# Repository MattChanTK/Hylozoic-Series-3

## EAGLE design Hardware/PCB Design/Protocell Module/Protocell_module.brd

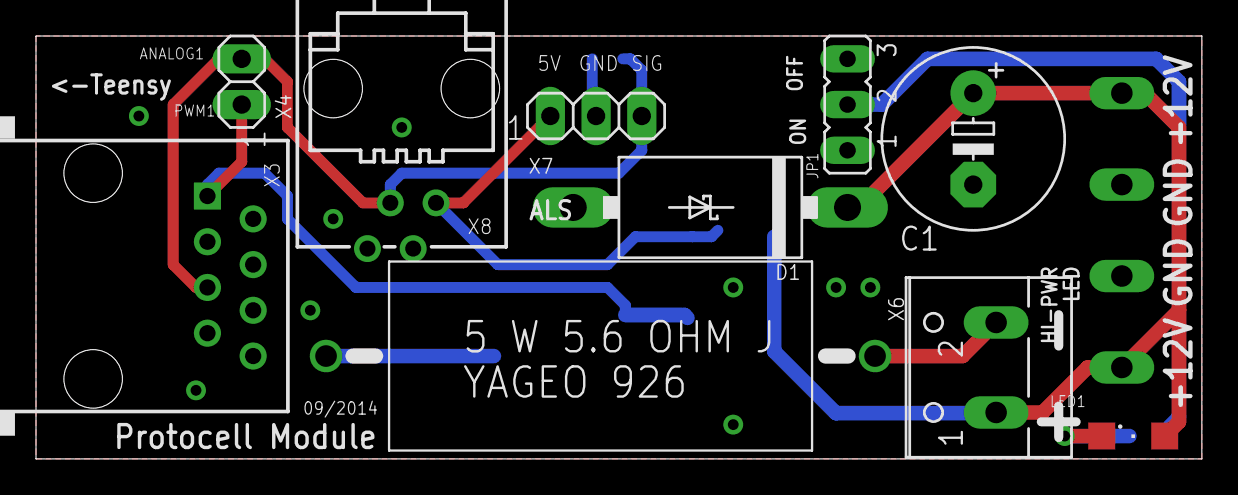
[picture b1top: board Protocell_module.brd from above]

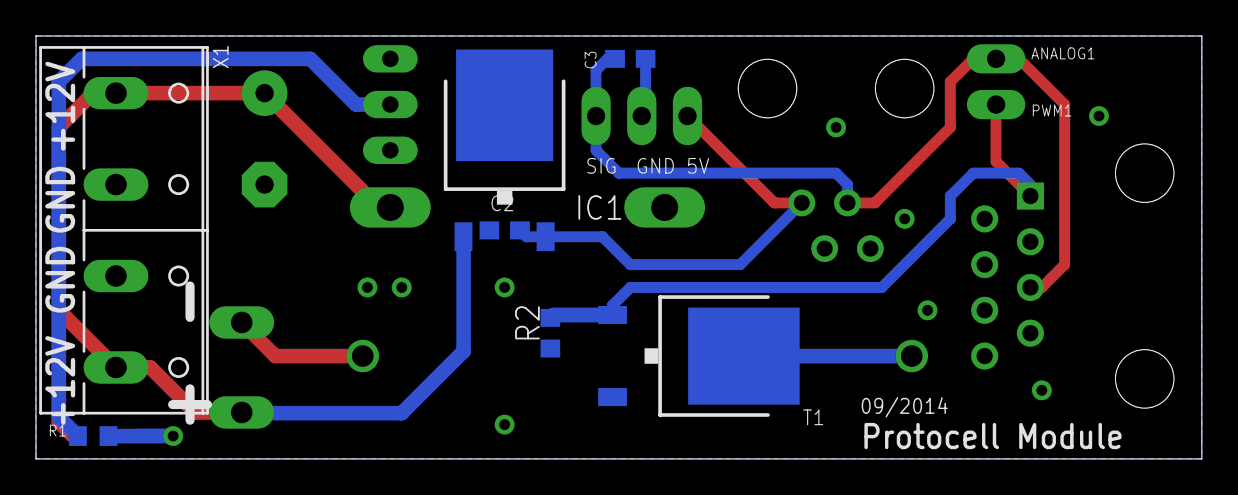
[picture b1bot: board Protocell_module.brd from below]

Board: 2 copper layers, 64.8 x 23.5 mm, 17 parts (7 on the bottom side), 9 nets.

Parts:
C1: 470uF; E5-10,5
C2, C3: 1uF; C0603
D1: SB540E-G; DO201T15
IC1: MC7805BDTRKG; DPACK_3
JP1: JP2
LED1: SML1206
R1: 470; R0603
R2: 4.7k; R0603
R3: 5.6; YAGEO_SQP500JB
T1: DPACK
X1: W237-4P
X3: RJ45-8X; RJ45-NO-SHIELD
X4: 1X02
X6: W237-102
X7: 1X03
X8: 558872-1

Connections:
+5V: C2.1, IC1.3, X7.1, X8.1
+12V: C1.+, D1.C, IC1.1, LED1.A, X1.1, X1.4, X6.1
ANALOG1: C3.1, X3.5, X4.2, X7.3, X8.3
GND: C1.-, C2.2, C3.2, D1.A, IC1.4, JP1.1, R2.1, T1.3, X1.2, X1.3, X7.2, X8.2
unnamed: R3.1, T1.2
unnamed: R3.2, X6.2
unnamed: LED1.C, R1.2
PWM1: R2.2, T1.1, X3.1, X4.1
PWR_LED_GND: JP1.2, R1.1

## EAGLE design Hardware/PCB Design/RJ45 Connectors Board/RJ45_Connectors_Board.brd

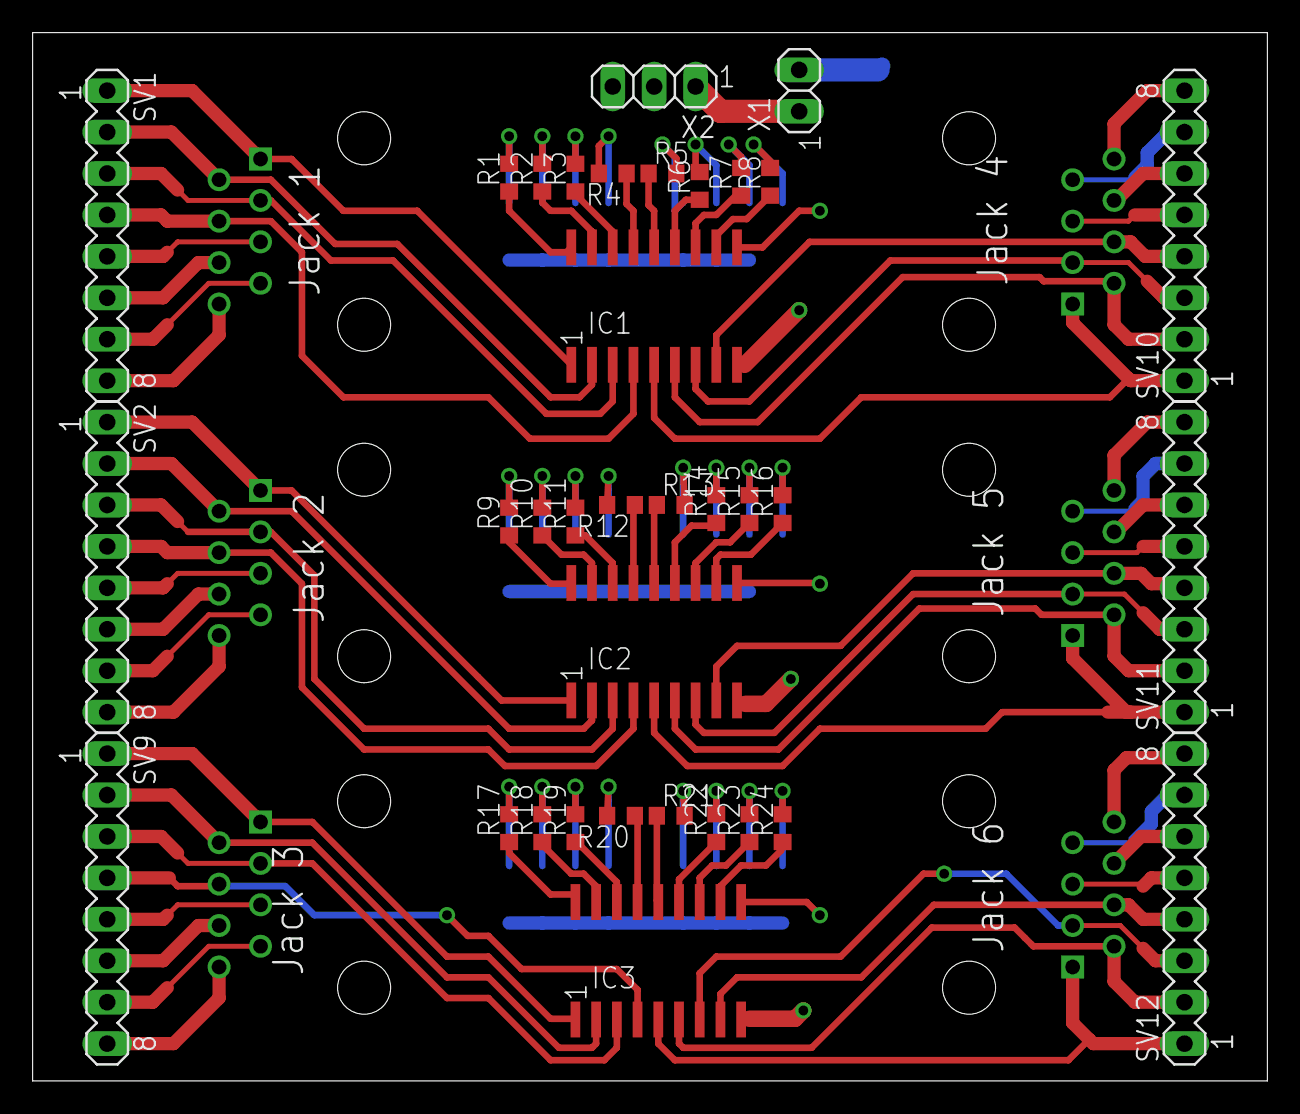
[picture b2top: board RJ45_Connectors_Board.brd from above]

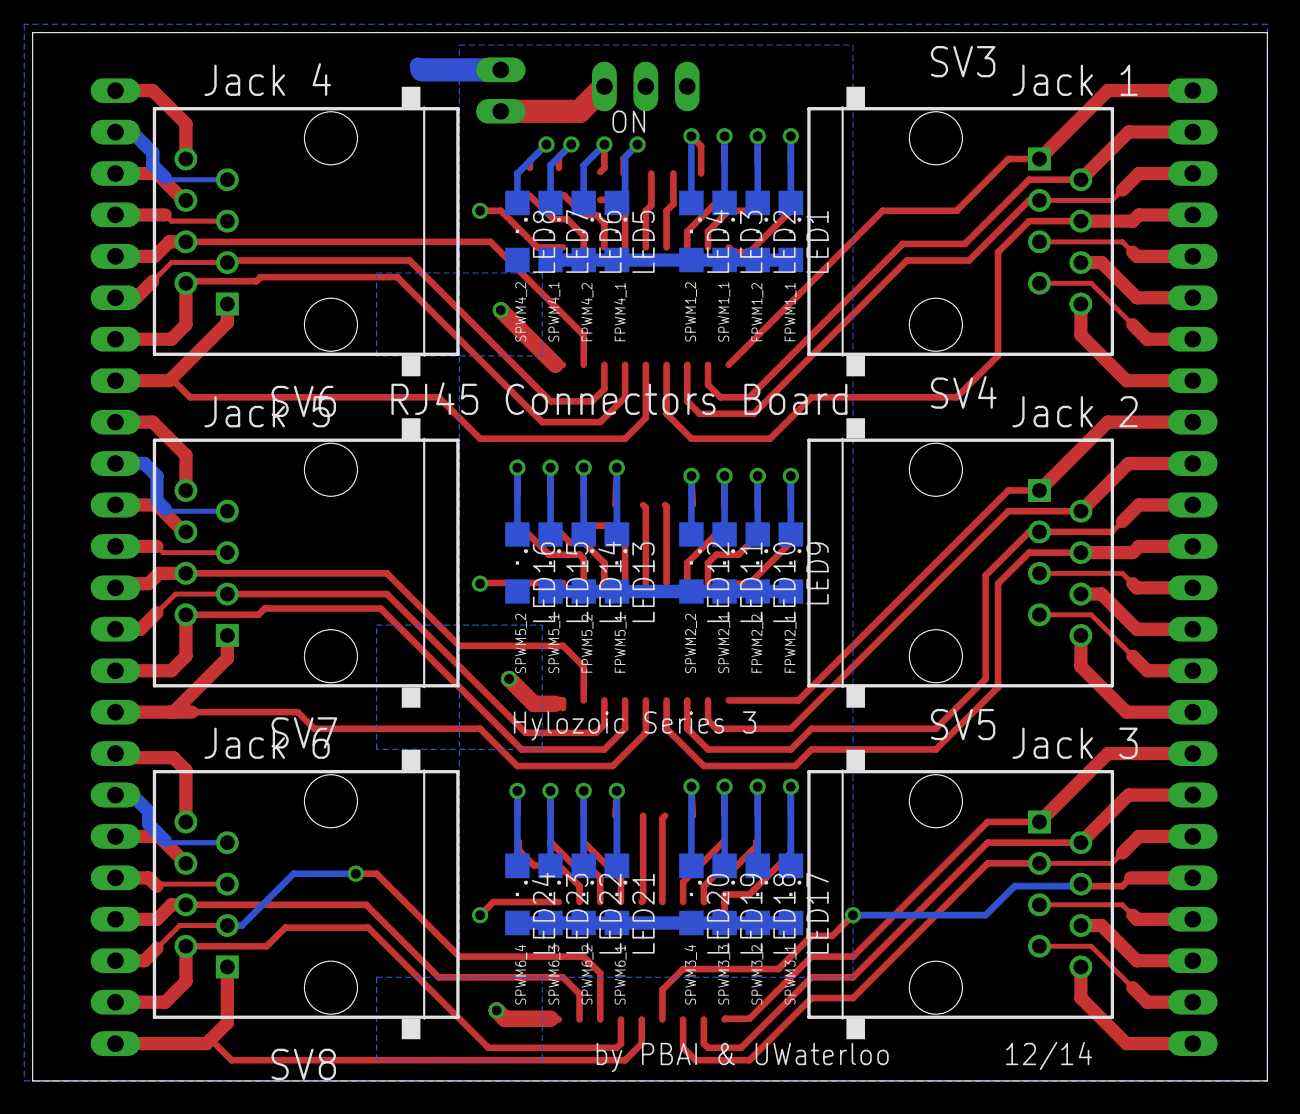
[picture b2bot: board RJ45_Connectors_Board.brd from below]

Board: 2 copper layers, 75.7 x 64.3 mm, 65 parts (30 on the bottom side), 99 nets.

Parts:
IC1, IC2, IC3: SOP18
LED1, LED2, LED3, LED4, LED5, LED6, LED7, LED8, LED9, LED10, LED11, LED12, LED13, LED14, LED15, LED16, LED17, LED18, LED19, LED20, LED21, LED22, LED23, LED24: SML1206
R1, R2, R3, R4, R5, R6, R7, R8, R9, R10, R11, R12, R13, R14, R15, R16, R17, R18, R19, R20, R21, R22, R23, R24: 470; R0603
SV1, SV2, SV9, SV10, SV11, SV12: MA08-1
SV3, SV4, SV5, SV6, SV7, SV8: RJ45-8X; RJ45-NO-SHIELD
X1: 1X02
X2: 1X03

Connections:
+5V: IC1.10, IC2.10, IC3.10, LED1.A, LED2.A, LED3.A, LED4.A, LED5.A, LED6.A, LED7.A, LED8.A, LED9.A, LED10.A, LED11.A, LED12.A, LED13.A, LED14.A, LED15.A, LED16.A, LED17.A, LED18.A, LED19.A, LED20.A, LED21.A, LED22.A, LED23.A, LED24.A, X2.2
+5VJUMP: X1.1, X2.1
A0: SV8.5, SV12.5
A1: SV8.6, SV12.6
A2: SV7.5, SV11.5
A3: SV7.6, SV11.6
A8: SV6.5, SV10.5
A9: SV6.6, SV10.6
A11: SV1.5, SV3.5
A12: SV2.5, SV4.5
A13: SV1.6, SV3.6
A15: SV2.6, SV4.6
A16: SV5.5, SV9.5
A17: SV5.6, SV9.6
FPWM_1_1: IC1.1, SV1.1, SV3.1
FPWM_1_2: IC1.2, SV1.2, SV3.2
FPWM_2_1: IC2.1, SV2.1, SV4.1
FPWM_2_2: IC2.2, SV2.2, SV4.2
FPWM_4_1: IC1.5, SV6.1, SV10.1
FPWM_4_2: IC1.6, SV6.2, SV10.2
FPWM_5_1: IC2.5, SV7.1, SV11.1
FPWM_5_2: IC2.6, SV7.2, SV11.2
GND: IC1.9, IC2.9, IC3.9, X1.2
MUL_SCL_1: SV1.7, SV3.7
MUL_SCL_2: SV2.7, SV4.7
MUL_SCL_3: SV5.7, SV9.7
MUL_SCL_4: SV6.7, SV10.7
MUL_SCL_5: SV7.7, SV11.7
MUL_SCL_6: SV8.7, SV12.7
MUL_SDA_1: SV1.8, SV3.8
MUL_SDA_2: SV2.8, SV4.8
MUL_SDA_3: SV5.8, SV9.8
MUL_SDA_4: SV6.8, SV10.8
MUL_SDA_5: SV7.8, SV11.8
MUL_SDA_6: SV8.8, SV12.8
unnamed: IC1.18, R1.1
unnamed: LED1.C, R1.2
unnamed: IC1.17, R2.1
unnamed: IC1.16, R3.1
unnamed: IC1.15, R4.1
unnamed: IC1.14, R5.1
unnamed: IC1.13, R6.1
unnamed: IC1.12, R7.1
unnamed: IC1.11, R8.1
unnamed: LED2.C, R2.2
unnamed: LED3.C, R3.2
unnamed: LED4.C, R4.2
unnamed: LED5.C, R5.2
unnamed: LED6.C, R6.2
unnamed: LED7.C, R7.2
unnamed: LED8.C, R8.2
unnamed: IC2.18, R9.1
unnamed: LED9.C, R9.2
unnamed: IC2.17, R10.1
unnamed: IC2.16, R11.1
unnamed: IC2.15, R12.1
unnamed: IC2.14, R13.1
unnamed: IC2.13, R14.1
unnamed: IC2.12, R15.1
unnamed: IC2.11, R16.1
unnamed: LED10.C, R10.2
unnamed: LED11.C, R11.2
unnamed: LED12.C, R12.2
unnamed: LED13.C, R13.2
unnamed: LED14.C, R14.2
unnamed: LED15.C, R15.2
unnamed: LED16.C, R16.2
unnamed: IC3.18, R17.1
unnamed: LED17.C, R17.2
unnamed: IC3.17, R18.1
unnamed: IC3.16, R19.1
unnamed: IC3.15, R20.1
unnamed: IC3.14, R21.1
unnamed: IC3.13, R22.1
unnamed: IC3.12, R23.1
unnamed: IC3.11, R24.1
unnamed: LED18.C, R18.2
unnamed: LED19.C, R19.2
unnamed: LED20.C, R20.2
unnamed: LED21.C, R21.2
unnamed: LED22.C, R22.2
unnamed: LED23.C, R23.2
unnamed: LED24.C, R24.2
SPWM_1_1: IC1.3, SV1.3, SV3.3
SPWM_1_2: IC1.4, SV1.4, SV3.4
SPWM_2_1: IC2.3, SV2.3, SV4.3
SPWM_2_2: IC2.4, SV2.4, SV4.4
SPWM_3_1: IC3.1, SV5.1, SV9.1
SPWM_3_2: IC3.2, SV5.2, SV9.2
SPWM_3_3: IC3.3, SV5.3, SV9.3
SPWM_3_4: IC3.4, SV5.4, SV9.4
SPWM_4_1: IC1.7, SV6.3, SV10.3
SPWM_4_2: IC1.8, SV6.4, SV10.4
SPWM_5_1: IC2.7, SV7.3, SV11.3
SPWM_5_2: IC2.8, SV7.4, SV11.4
SPWM_6_1: IC3.5, SV8.1, SV12.1
SPWM_6_2: IC3.6, SV8.2, SV12.2
SPWM_6_3: IC3.7, SV8.3, SV12.3
SPWM_6_4: IC3.8, SV8.4, SV12.4

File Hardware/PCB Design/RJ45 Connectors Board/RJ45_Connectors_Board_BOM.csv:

"Qty";"Value";"Device";"Package";"Parts";"Description";"MF";"MPN";"OC_FARNELL";"OC_NEWARK";
"24";"";"LEDSML1206";"SML1206";"LED1, LED2, LED3, LED4, LED5, LED6, LED7, LED8, LED9, LED10, LED11, LED12, LED13, LED14, LED15, LED16, LED17, LED18, LED19, LED20, LED21, LED22, LED23, LED24";"LED";"";"";"";"";
"6";"";"MA08-1";"MA08-1";"SV1, SV2, SV9, SV10, SV11, SV12";"PIN HEADER";"";"";"unknown";"unknown";
"1";"";"PINHD-1X2";"1X02";"X1";"PIN HEADER";"";"";"";"";
"1";"";"PINHD-1X3";"1X03";"X2";"PIN HEADER";"";"";"";"";
"3";"";"ULN2803AFWG";"SOP18";"IC1, IC2, IC3";"DRIVER ARRAY";"";"";"";"";
"24";"470";"R-US_R0603";"R0603";"R1, R2, R3, R4, R5, R6, R7, R8, R9, R10, R11, R12, R13, R14, R15, R16, R17, R18, R19, R20, R21, R22, R23, R24";"RESISTOR, American symbol";"";"";"";"";
"6";"RJ45-8X";"RJ45-8X";"RJ45-NO-SHIELD";"SV3, SV4, SV5, SV6, SV7, SV8";"CORCOM Modular RJ Jacks No Shield";"";"RJ45-8X";"unknown";"16R6101";

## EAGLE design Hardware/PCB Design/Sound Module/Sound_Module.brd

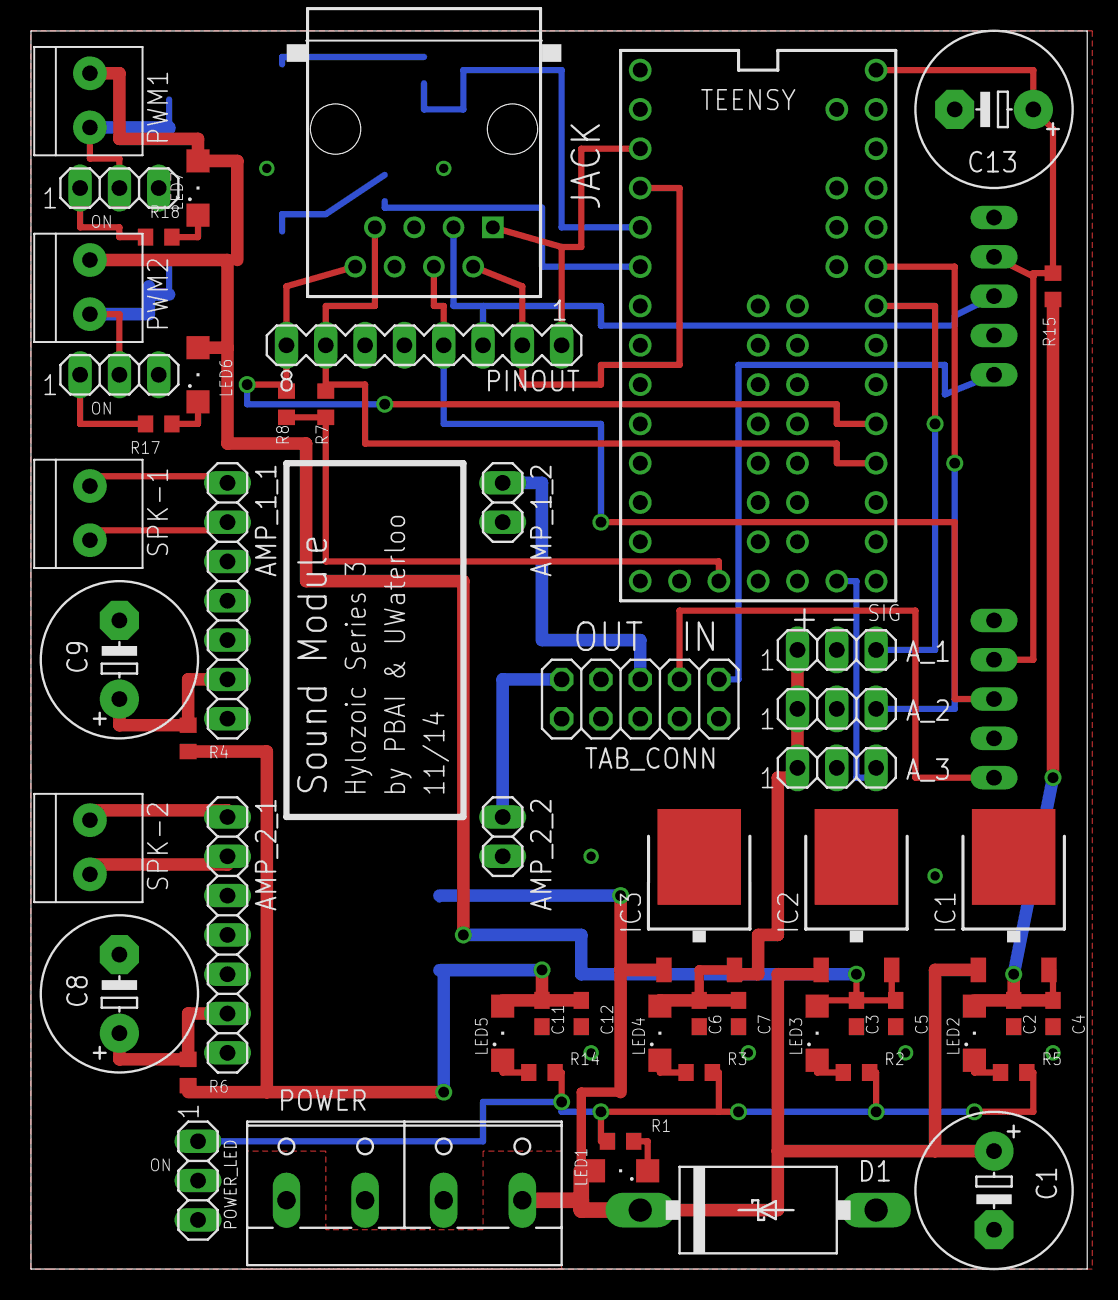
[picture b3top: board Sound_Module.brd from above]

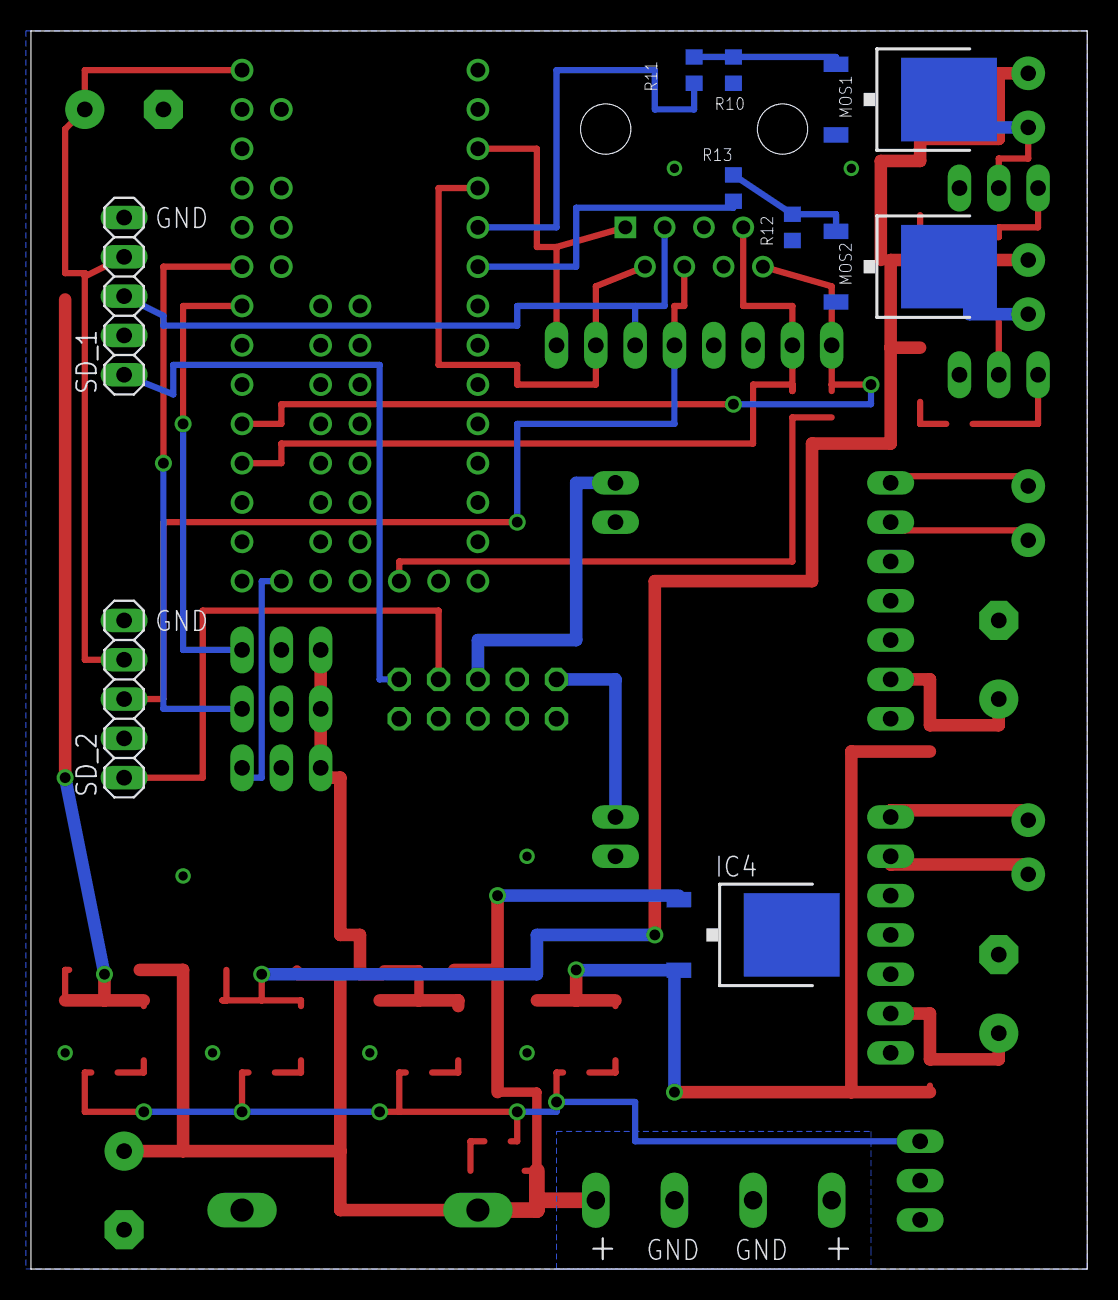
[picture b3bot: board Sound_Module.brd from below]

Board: 2 copper layers, 68.2 x 80.0 mm, 63 parts (9 on the bottom side), 43 nets.

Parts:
AMP_1_1, AMP_2_1: 1X07
AMP_1_2, AMP_2_2: 1X02
A_1, A_2, A_3: 1X03
C1: 2000uF; E5-10,5
C2, C3, C6, C11: 1uF; C0603
C4, C5, C7, C12: 100nF; C0603
C8, C9, C13: 470uF; E5-10,5
D1: SB540E-G; DO201T15
IC1, IC2, IC3, IC4: DPACK_3
JACK: RJ45-6L-B; RJ45-NO-SHIELD
LED1, LED2, LED3, LED4, LED5, LED6, LED7: SML1206
MOS1, MOS2: DPACK
PINOUT: MA08-1
POWER: W237-4P
POWER_LED: 1X03
PWM1, PWM2: 1X2-3.5MM
R1, R2, R3, R5, R14, R17, R18: 470; R0603
R4, R6, R15: 10; R0603
R7, R8: 2.2k; R0603
R10, R12: 4.7K; R0603
R11, R13: 1K; R0603
SD_1, SD_2: 1X05
SPK-1, SPK-2: 1X2-3.5MM
TAB_CONN: 2X05
TEENSY: AUDIO BOARD; TEENSY_3.1_ALLPINS
X2, X3: 1X03

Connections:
3.3V: R7.2, R8.2, TEENSY.3.3V, TEENSY.3.3V1, TEENSY.3.3V2
5VFILT: C13.+, R15.1, SD_1.4, SD_2.4, TEENSY.VIN
+5V_1: C2.1, C4.1, IC1.3, LED2.A, R15.2
+5V_2: C3.1, C5.1, IC2.3, LED3.A, LED6.A, LED7.A, PWM1.2, PWM2.2
+5V_3: A_1.1, A_2.1, A_3.1, C6.1, C7.1, IC3.3, LED4.A
+5V_4: C11.1, C12.1, IC4.3, LED5.A, R4.2, R6.2
+12V: C1.+, D1.C, IC1.1, IC2.1, IC3.1, IC4.1, LED1.A, POWER.1, POWER.4
AMP_1_VIN: AMP_1_1.6, C9.+, R4.1
AMP_2_VIN: AMP_2_1.6, C8.+, R6.1
DPEAK_1: JACK.3, PINOUT.3, SD_1.3
DPEAK_2: JACK.4, PINOUT.4, SD_2.3
DTRIG_1: JACK.1, PINOUT.1, TEENSY.1
DTRIG_2: JACK.2, PINOUT.2, TEENSY.2
FPWM_1_1: R11.2, TEENSY.3
FPWM_1_2: R13.2, TEENSY.4
GND: AMP_1_1.5, AMP_1_2.2, AMP_2_1.5, AMP_2_2.2, A_1.2, A_2.2, A_3.2, C1.-, C2.2, C3.2, C4.2, C5.2, C6.2, C7.2, C8.-, C9.-, C11.2, C12.2, C13.-, D1.A, IC1.4, IC2.4, IC3.4, IC4.4, MOS1.3, MOS2.3, POWER.2, POWER.3, POWER_LED.2, R10.1, R12.1, SD_1.5, SD_2.5, TAB_CONN.2, TAB_CONN.4, TAB_CONN.7, TEENSY.GND, TEENSY.GND1, TEENSY.GND2
IN_1+: AMP_1_2.1, TAB_CONN.5
IN_2+: AMP_2_2.1, TAB_CONN.9
LED_JUMP_POW: POWER_LED.1, R1.1, R2.1, R3.1, R5.1, R14.1
MIC_1: SD_1.1, TAB_CONN.1
MIC_2: SD_2.1, TAB_CONN.3
unnamed: MOS2.1, R12.2, R13.1
unnamed: LED3.C, R2.2
unnamed: LED4.C, R3.2
unnamed: MOS1.1, R10.2, R11.1
unnamed: MOS1.2, PWM1.1, X2.2
unnamed: LED6.C, R17.2
unnamed: MOS2.2, PWM2.1, X3.2
unnamed: LED5.C, R14.2
unnamed: LED7.C, R18.2
unnamed: LED1.C, R1.2
unnamed: R18.1, X2.1
unnamed: R17.1, X3.1
unnamed: LED2.C, R5.2
SCL: JACK.7, PINOUT.7, R7.1, TEENSY.16/A2
SDA: JACK.8, PINOUT.8, R8.1, TEENSY.17/A3
SIG_1: A_1.3, TEENSY.20/A6
SIG_2: A_2.3, TEENSY.21/A7
SIG_3: A_3.3, TEENSY.A14
SPK_1+: AMP_1_1.1, SPK-1.2
SPK_1-: AMP_1_1.2, SPK-1.1
SPK_2+: AMP_2_1.1, SPK-2.2
SPK_2-: AMP_2_1.2, SPK-2.1

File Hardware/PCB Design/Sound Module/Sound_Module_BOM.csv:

"Qty";"Value";"Device";"Package";"Parts";"Description";"MF";"MPN";"OC_FARNELL";"OC_NEWARK";
"7";"";"LEDSML1206";"SML1206";"LED1, LED2, LED3, LED4, LED5, LED6, LED7";"LED";"";"";"";"";
"1";"";"MA08-1";"MA08-1";"PINOUT";"PIN HEADER";"";"";"unknown";"unknown";
"4";"";"MC7805BDTRKG";"DPACK_3";"IC1, IC2, IC3, IC4";"1A Positive Voltage Regulators";"";"";"";"";
"2";"";"NTD5867NLT4G";"DPACK";"MOS1, MOS2";"MOS FET";"";"";"";"";
"2";"";"PINHD-1X2";"1X02";"AMP_1_2, AMP_2_2";"PIN HEADER";"";"";"";"";
"6";"";"PINHD-1X3";"1X03";"A_1, A_2, A_3, POWER_LED, X2, X3";"PIN HEADER";"";"";"";"";
"2";"";"PINHD-1X5";"1X05";"SD_1, SD_2";"PIN HEADER";"";"";"";"";
"2";"";"PINHD-1X7";"1X07";"AMP_1_1, AMP_2_1";"PIN HEADER";"";"";"";"";
"1";"";"PINHD-2X5";"2X05";"TAB_CONN";"PIN HEADER";"";"";"";"";
"1";"";"W237-04P";"W237-4P";"POWER";"WAGO SREW CLAMP";"";"";"unknown";"unknown";
"3";"10";"R-US_R0603";"R0603";"R4, R6, R15";"RESISTOR, American symbol";"";"";"";"";
"4";"100nF";"C-USC0603";"C0603";"C4, C5, C7, C12";"CAPACITOR, American symbol";"";"";"";"";
"2";"1K";"R-US_R0603";"R0603";"R11, R13";"RESISTOR, American symbol";"";"";"";"";
"4";"1X2-3.5MM";"1X2-3.5MM";"1X2-3.5MM";"PWM1, PWM2, SPK-1, SPK-2";"3.5mm Terminal block";"";"";"";"";
"4";"1uF";"C-USC0603";"C0603";"C2, C3, C6, C11";"CAPACITOR, American symbol";"";"";"";"";
"2";"2.2k";"R-US_R0603";"R0603";"R7, R8";"RESISTOR, American symbol";"";"";"";"";
"1";"2000uF";"CPOL-USE5-10.5";"E5-10,5";"C1";"POLARIZED CAPACITOR, American symbol";"";"";"";"";
"2";"4.7K";"R-US_R0603";"R0603";"R10, R12";"RESISTOR, American symbol";"";"";"";"";
"7";"470";"R-US_R0603";"R0603";"R1, R2, R3, R5, R14, R17, R18";"RESISTOR, American symbol";"";"";"";"";
"3";"470uF";"CPOL-USE5-10.5";"E5-10,5";"C8, C9, C13";"POLARIZED CAPACITOR, American symbol";"";"";"";"";
"1";"AUDIO BOARD";"TEENSY_3.1_ALL_PINS_AND_PADS";"TEENSY_3.1_ALLPINS";"TEENSY";"Footprint for Teensy 3.1 board using all pads and all through-holes. Pads need a 2x7 0.1" SMD header.";"";"";"";"";
"1";"RJ45-6L-B";"RJ45-6L-B";"RJ45-NO-SHIELD";"JACK";"CORCOM Modular RJ Jacks No Shield";"";"RJ45-6L-B";"unknown";"16R6090";
"1";"SB540E-G";"SB540E-G";"DO201T15";"D1";"SCHOTTKY BARRIER RECTIFIER 3.0 AMPERES 20, 30, 40 VOLT";"";"";"";"";

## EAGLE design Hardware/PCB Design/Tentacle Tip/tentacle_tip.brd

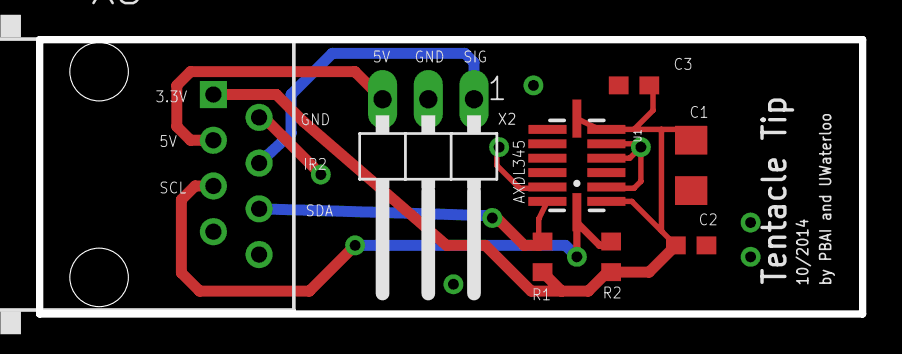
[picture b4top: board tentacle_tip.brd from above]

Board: 2 copper layers, 45.7 x 15.2 mm, 8 parts (0 on the bottom side), 6 nets.

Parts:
C1: 10uF; C1206
C2, C3: 0.1uF; C0603
R1, R2: 2.2k; R0603
U1: ADXL345; LGA14_LONG
X2: 1X03/90
X3: RJ45-8X; RJ45-NO-SHIELD

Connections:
+3.3V: C1.1, C2.1, C3.1, R1.2, R2.2, U1.1, U1.6, U1.7, X3.1
+5V: X2.3, X3.3
GND: C1.2, C2.2, C3.2, U1.2, U1.4, U1.5, U1.12, X2.2, X3.2
IR2: X2.1, X3.4
SCL: R2.1, U1.14, X3.5
SDA: R1.1, U1.13, X3.6

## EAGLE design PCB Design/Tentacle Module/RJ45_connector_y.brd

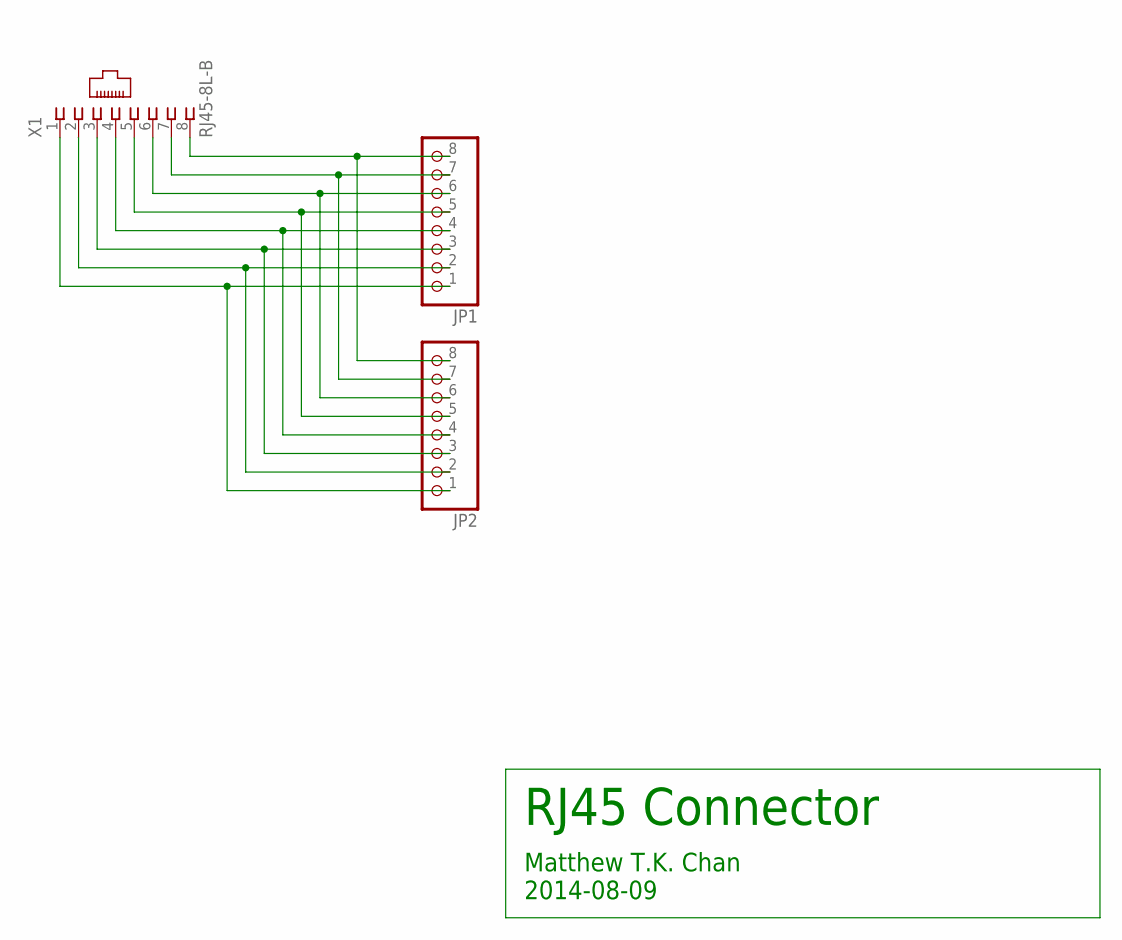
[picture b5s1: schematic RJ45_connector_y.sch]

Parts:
JP1, JP2: PINHD-1X8; 1X08
X1: RJ45-8L-B; RJ45-NO-SHIELD

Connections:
unnamed: JP1.8, JP2.8, X1.8
unnamed: JP1.7, JP2.7, X1.7
unnamed: JP1.6, JP2.6, X1.6
unnamed: JP1.5, JP2.5, X1.5
unnamed: JP1.4, JP2.4, X1.4
unnamed: JP1.3, JP2.3, X1.3
unnamed: JP1.2, JP2.2, X1.2
unnamed: JP1.1, JP2.1, X1.1

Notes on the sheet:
RJ45 Connector
Matthew T.K. Chan 2014-08-09

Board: 2 copper layers, 3 parts (0 on the bottom side), 8 nets, no tracks yet.

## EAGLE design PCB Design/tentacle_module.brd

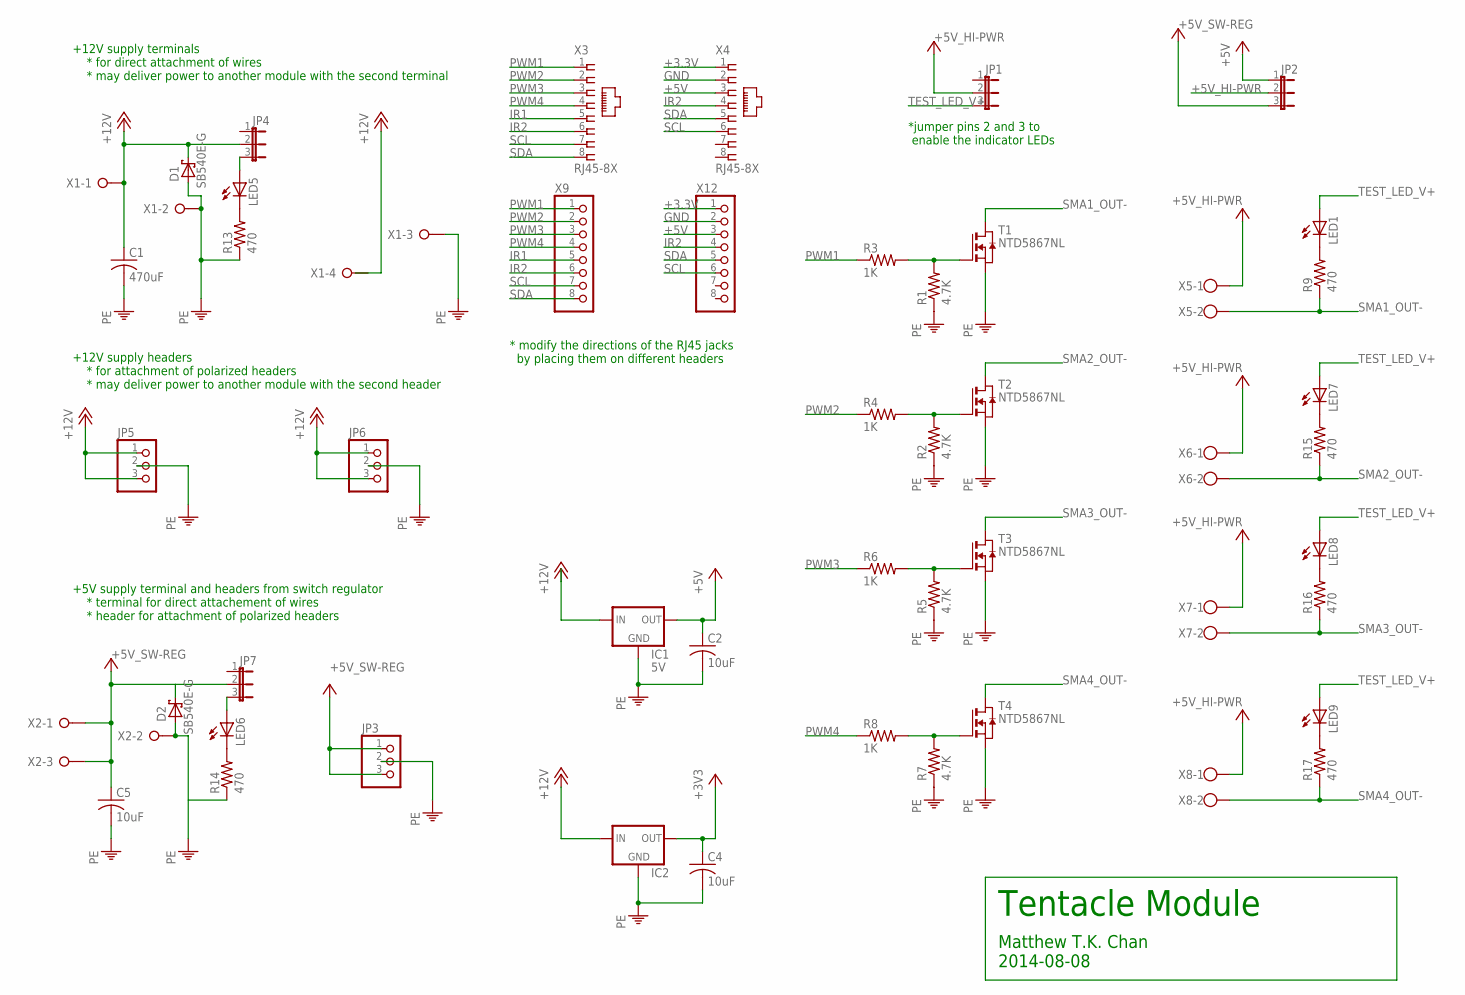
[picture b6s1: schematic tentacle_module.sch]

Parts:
C1: 470uF; C1206
C2, C4, C5: 10uF; C1206
D1, D2: SB540E-G; DO201T15
IC1: 5V; TO220L1
IC2: 78XXSHORIZONTAL; TO220L1
JP1, JP2, JP4, JP7: JP2E; JP2
JP3, JP5, JP6: PINHD-1X3/90; 1X03/90
LED1, LED5, LED6, LED7, LED8, LED9: LEDSML1206; SML1206
R1, R2, R5, R7: 4.7K; R1206
R3, R4, R6, R8: 1K; R1206
R9, R13, R14, R15, R16, R17: 470; R1206
T1, T2, T3, T4: NTD5867NL; DPACK
X1: W237-04P; W237-4P
X2: W237-03P; W237-133
X3, X4: RJ45-8X; RJ45-NO-SHIELD
X5, X6, X7, X8: W237-102
X9, X12: PINHD-1X8/90; 1X08/90

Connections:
+3.3V: X4.1, X12.1
+3V3: C4.1, IC2.3 (OUT)
+5V: C2.1, IC1.3 (OUT), JP1.2, JP2.1, JP2.3, X4.3, X12.3
+5V_HI-PWR: JP2.2, X5.1, X6.1, X7.1, X8.1
+5V_SW-REG: C5.1, D2.C, JP3.1, JP3.3, X2.1, X2.3
+12V: C1.1, D1.C, IC1.1 (IN), IC2.1 (IN), JP4.2, JP5.1, JP5.3, JP6.1, JP6.3, X1.1
+12V1: JP7.2
GND: C1.2, C2.2, C4.2, C5.2, D1.A, D2.A, IC1.2 (GND), IC2.2 (GND), JP3.2, JP5.2, JP6.2, R1.1, R2.1, R5.1, R7.1, R13.1, T1.3 (S), T2.3 (S), T3.3 (S), T4.3 (S), X1.2, X1.3, X2.2, X4.2, X12.2
GND1: R14.1
IR1: X3.5, X9.5
IR2: X3.6, X4.4, X9.6, X12.4
unnamed: R2.2, R4.2, T2.1 (G)
unnamed: R5.2, R6.2, T3.1 (G)
unnamed: R7.2, R8.2, T4.1 (G)
unnamed: R1.2, R3.2, T1.1 (G)
unnamed: LED1.C, R9.2
unnamed: LED5.C, R13.2
unnamed: JP4.3, LED5.A
unnamed: LED6.C, R14.2
unnamed: JP7.3, LED6.A
unnamed: LED7.C, R15.2
unnamed: LED8.C, R16.2
unnamed: LED9.C, R17.2
PWM1: R3.1, X3.1, X9.1
PWM2: R4.1, X3.2, X9.2
PWM3: R6.1, X3.3, X9.3
PWM4: R8.1, X3.4, X9.4
SCL: X3.7, X4.6, X9.7, X12.6
SDA: X3.8, X4.5, X9.8, X12.5
SMA1_OUT-: R9.1, T1.2 (D), X5.2
SMA2_OUT-: R15.1, T2.2 (D), X6.2
SMA3_OUT-: R16.1, T3.2 (D), X7.2
SMA4_OUT-: R17.1, T4.2 (D), X8.2
TEST_LED_V+: JP1.3, LED1.A, LED7.A, LED8.A, LED9.A

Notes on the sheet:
Tentacle Module
Matthew T.K. Chan 2014-08-08
+12V supply headers * for attachment of polarized headers * may deliver power to another module with the second header
+12V supply terminals * for direct attachment of wires * may deliver power to another module with the second terminal
+5V supply terminal and headers from switch regulator * terminal for direct attachement of wires * header for attachment of polarized headers
*jumper pins 2 and 3 to enable the indicator LEDs
* modify the directions of the RJ45 jacks by placing them on different headers

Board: 2 copper layers, 49 parts (10 on the bottom side), 32 nets, no tracks yet.
